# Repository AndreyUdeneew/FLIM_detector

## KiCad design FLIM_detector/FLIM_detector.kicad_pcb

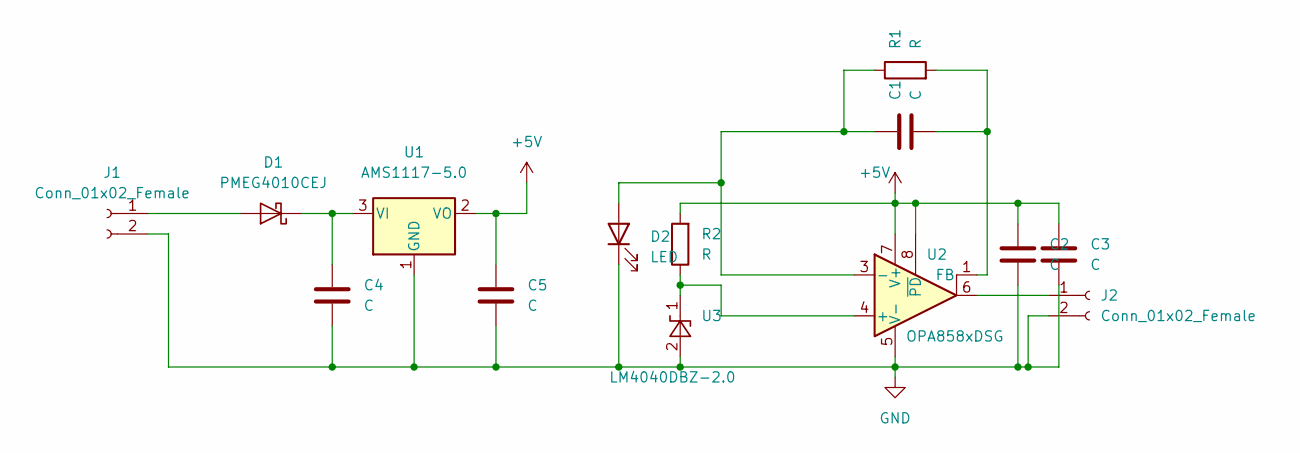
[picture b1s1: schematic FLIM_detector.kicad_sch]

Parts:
C1, C2, C3: C; C_0201_0603Metric
C4, C5: C; C_0603_1608Metric_Pad1.08x0.95mm_HandSolder
D1: PMEG4010CEJ; D_SOD-323F
D2: LED; LED_D5.0mm_Clear
J1, J2: Conn_01x02_Female; PinHeader_1x02_P2.54mm_Vertical
R1: R; R_0201_0603Metric
R2: R; R_0402_1005Metric_Pad0.72x0.64mm_HandSolder
U1: AMS1117-5.0; SOT-223-3_TabPin2
U2: OPA858xDSG; WSON-8-1EP_2x2mm_P0.5mm_EP0.9x1.6mm_ThermalVias
U3: LM4040DBZ-2.0; SOT-23

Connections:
+5V: C2.2, C3.2, C5.2, R2.2, U1.2 (VO), U2.7 (V+), U2.8 (~PD)
GND: C2.1, C3.1, C4.1, C5.1, D2.1 (K), J1.2, J2.2, U1.1 (GND), U2.5 (V-), U2.9 (V-), U3.2 (A)
unnamed: C1.2, R1.2, U2.1 (FB)
unnamed: C4.2, D1.1 (K), U1.3 (VI)
unnamed: D1.2 (A), J1.1
unnamed: J2.1, U2.6
unnamed: R2.1, U2.4 (+), U3.1 (K)
unnamed: C1.1, D2.2 (A), R1.1, U2.3 (-)

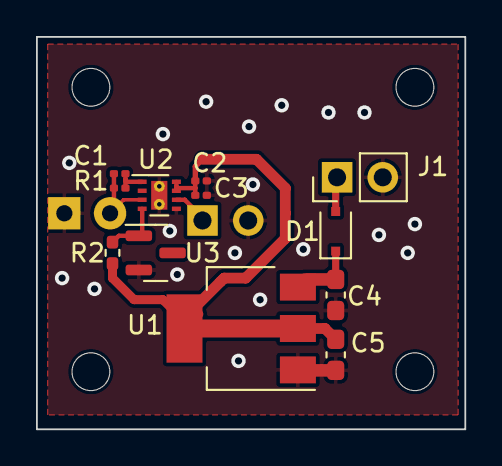
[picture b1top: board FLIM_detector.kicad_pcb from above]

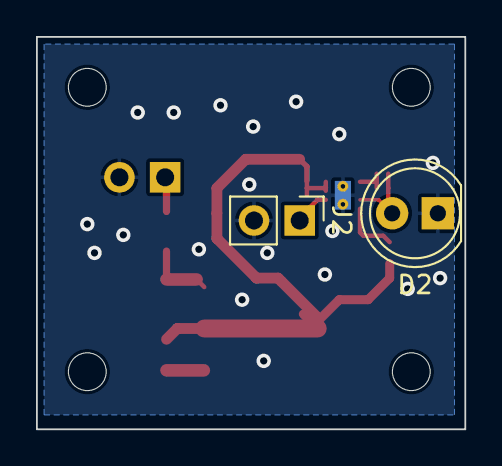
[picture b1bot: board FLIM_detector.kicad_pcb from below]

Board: 2 copper layers, 23.8 x 21.8 mm, 14 parts (2 on the bottom side), 8 nets.

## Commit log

2022-05-06 v0.1 circuit was created
2022-05-06 v0.2 components on PCB were decomposed
2022-05-06 v0.3 power source waas added, some components were decreased into 0402
2022-05-07 v0.4 input shotthy was added
2022-05-09 v0.5 routing, polygons and mounting holes were added
2022-05-10 v0.6 PCB size was decreased
2022-05-10 v0.7 power connector was flipped
2022-05-11 v0.8 Routing was optimized
2022-05-12 v0.81 some changes
2022-05-13 v0.9 subcompleted
2022-05-14 v0.91 DRC was conducted
2022-05-16 v0.92 silk was corrected
2022-05-16 v0.93 Gerbers and drl were created
